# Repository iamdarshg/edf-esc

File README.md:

# EDF-ESC

Open hardware and firmware for a compact 98 mm × 58 mm, four-layer board with
two independent 6S sensorless BLDC/EDF controller channels.

> **Engineering prototype — do not fabricate or connect a battery.** The CAD
> currently contains documented placement placeholders, open nets, and DRC
> violations. It is not a validated 150 A design. See
> [`docs/cad-status.md`](docs/cad-status.md) for the exact blockers.

## Design targets

- two electrically independent power paths; no shared 300 A PCB segment;
- 18 × SFS06R025GF per channel, three devices per switch;
- DRV8300D gate driver and PY32F030K28U6TR controller per channel;
- high-side copper-shunt/INA190A3 current sensing with four-wire calibration;
- sensorless six-step control with PWM throttle and shared SPI/separate CS;
- shared 12 V gate supply, 5 V/8 A characterization-target BEC, and 3.3 V logic;
- JLCPCB/LCSC-first sourcing with Mouser alternatives and top-side assembly;
- top-side CNC copper reinforcement for every high-current path.

## What works today

The calculation engine, BOM/pin-mux contracts, host protocol, commutation table,
startup/control state machine, zero-cross detector, protection model, and both
channel configuration contracts are covered by native tests. KiCad 7.0.11
parses the generated review CAD and exports plots.

```sh
python3 -m venv .venv
.venv/bin/pip install -e '.[test]'
make test
.venv/bin/python -m edf_esc.cad
```

## Repository map

- `hardware/` — deterministic KiCad review project and design-rule contracts
- `firmware/` — tested portable control core and PY32 pin/configuration contract
- `host/` — SPI framing reference
- `bom/` — primary and alternate sourcing tables
- `calculations/` — gate, MOSFET, shunt, copper, and BEC estimates
- `docs/` — architecture, protocol, safety status, and source ledger

The progression to powered testing is intentionally gated: inspection, gate-only
testing, current-limited low-voltage switching, 3S motor testing, restricted 6S,
then thermal/electrical characterization. A numerical current ceiling is not a
continuous-current rating.

## License

MIT. See [`LICENSE`](LICENSE). Component datasheets and vendor SDK files are not
redistributed unless their licenses permit it.

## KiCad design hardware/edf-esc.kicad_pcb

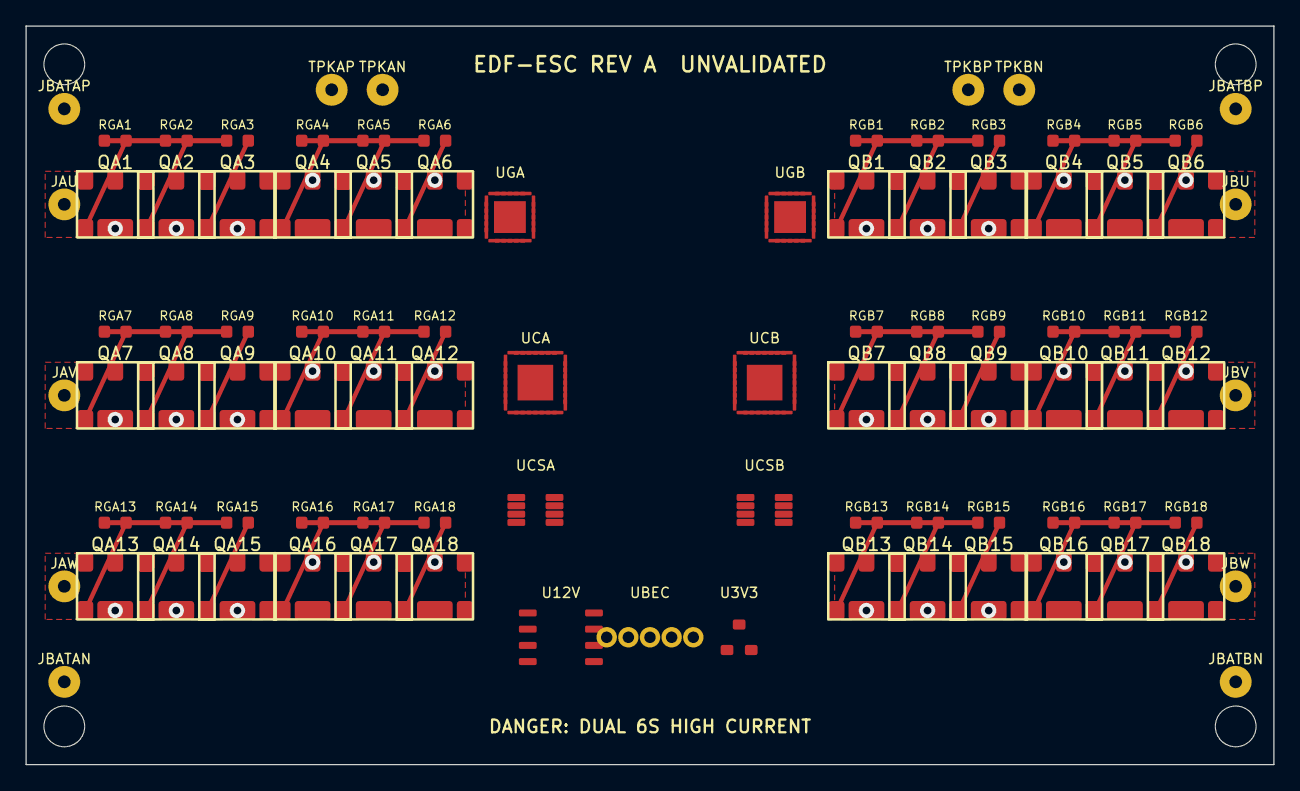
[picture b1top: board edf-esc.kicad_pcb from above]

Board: 4 copper layers, 98.0 x 58.0 mm, 99 parts (0 on the bottom side), 83 nets.

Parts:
H1, H2, H3, H4: M3; M3_NPTH
JAU: MOTOR_A_U; TESTPAD_2MM
JAV: MOTOR_A_V; TESTPAD_2MM
JAW: MOTOR_A_W; TESTPAD_2MM
JBATAN: BAT_A-; TESTPAD_2MM
JBATAP: BAT_A+; TESTPAD_2MM
JBATBN: BAT_B-; TESTPAD_2MM
JBATBP: BAT_B+; TESTPAD_2MM
JBU: MOTOR_B_U; TESTPAD_2MM
JBV: MOTOR_B_V; TESTPAD_2MM
JBW: MOTOR_B_W; TESTPAD_2MM
QA1, QA2, QA3, QA4, QA5, QA6, QA7, QA8, QA9, QA10, QA11, QA12, QA13, QA14, QA15, QA16, QA17, QA18: SFS06R025GF; PDFN56
QB1, QB2, QB3, QB4, QB5, QB6, QB7, QB8, QB9, QB10, QB11, QB12, QB13, QB14, QB15, QB16, QB17, QB18: SFS06R025GF; PDFN56
RGA1, RGA2, RGA3, RGA4, RGA5, RGA6, RGA7, RGA8, RGA9, RGA10, RGA11, RGA12, RGA13, RGA14, RGA15, RGA16, RGA17, RGA18: 4R7; R_0603
RGB1, RGB2, RGB3, RGB4, RGB5, RGB6, RGB7, RGB8, RGB9, RGB10, RGB11, RGB12, RGB13, RGB14, RGB15, RGB16, RGB17, RGB18: 4R7; R_0603
TPKAN: KELVIN_A-; TESTPAD_2MM
TPKAP: KELVIN_A+; TESTPAD_2MM
TPKBN: KELVIN_B-; TESTPAD_2MM
TPKBP: KELVIN_B+; TESTPAD_2MM
U3V3: XC6206P332MR; SOT23-3
U12V: XL1509-ADJ; SOIC8
UBEC: XL4016E1; TO220-5
UCA: PY32F030K28U6TR; QFN32
UCB: PY32F030K28U6TR; QFN32
UCSA: INA190A3IDDFR; TSOT23-8
UCSB: INA190A3IDDFR; TSOT23-8
UGA: DRV8300DRGER; QFN24
UGB: DRV8300DRGER; QFN24

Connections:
12V_GATE: UGA.4, UGB.4
12V_SW: U12V.1, U12V.2
+3V3: U3V3.2, UCA.1, UCB.1, UCSA.1, UCSA.2, UCSB.1, UCSB.2
BAT_A+: JBATAP.1, QA1.5, QA1.6, QA1.7, QA1.8, QA2.5, QA2.6, QA2.7, QA2.8, QA3.5, QA3.6, QA3.7, QA3.8, QA7.5, QA7.6, QA7.7, QA7.8, QA8.5, QA8.6, QA8.7, QA8.8, QA9.5, QA9.6, QA9.7, QA9.8, QA13.5, QA13.6, QA13.7, QA13.8, QA14.5, QA14.6, QA14.7, QA14.8, QA15.5, QA15.6, QA15.7, QA15.8, U12V.6, U12V.7, UBEC.4
BAT_A-: JBATAN.1, QA4.1, QA4.2, QA4.3, QA5.1, QA5.2, QA5.3, QA6.1, QA6.2, QA6.3, QA10.1, QA10.2, QA10.3, QA11.1, QA11.2, QA11.3, QA12.1, QA12.2, QA12.3, QA16.1, QA16.2, QA16.3, QA17.1, QA17.2, QA17.3, QA18.1, QA18.2, QA18.3
BAT_B+: JBATBP.1, QB1.5, QB1.6, QB1.7, QB1.8, QB2.5, QB2.6, QB2.7, QB2.8, QB3.5, QB3.6, QB3.7, QB3.8, QB7.5, QB7.6, QB7.7, QB7.8, QB8.5, QB8.6, QB8.7, QB8.8, QB9.5, QB9.6, QB9.7, QB9.8, QB13.5, QB13.6, QB13.7, QB13.8, QB14.5, QB14.6, QB14.7, QB14.8, QB15.5, QB15.6, QB15.7, QB15.8
BAT_B-: JBATBN.1, QB4.1, QB4.2, QB4.3, QB5.1, QB5.2, QB5.3, QB6.1, QB6.2, QB6.3, QB10.1, QB10.2, QB10.3, QB11.1, QB11.2, QB11.3, QB12.1, QB12.2, QB12.3, QB16.1, QB16.2, QB16.3, QB17.1, QB17.2, QB17.3, QB18.1, QB18.2, QB18.3
CURRENT_A: UCA.6, UCSA.5
CURRENT_B: UCB.6, UCSB.5
GND: U3V3.1, U12V.4, UBEC.1, UCA.16, UCA.31, UCA.33, UCB.16, UCB.31, UCB.33, UCSA.3, UCSA.4, UCSB.3, UCSB.4, UGA.5, UGA.6, UGA.25, UGB.5, UGB.6, UGB.25
G_A_UH: RGA1.1, RGA2.1, RGA3.1, UGA.19
G_A_UH_1: QA1.4, RGA1.2
G_A_UH_2: QA2.4, RGA2.2
G_A_UH_3: QA3.4, RGA3.2
G_A_UL: RGA4.1, RGA5.1, RGA6.1, UGA.11
G_A_UL_1: QA4.4, RGA4.2
G_A_UL_2: QA5.4, RGA5.2
G_A_UL_3: QA6.4, RGA6.2
G_A_VH: RGA7.1, RGA8.1, RGA9.1, UGA.16
G_A_VH_1: QA7.4, RGA7.2
G_A_VH_2: QA8.4, RGA8.2
G_A_VH_3: QA9.4, RGA9.2
G_A_VL: RGA10.1, RGA11.1, RGA12.1, UGA.10
G_A_VL_1: QA10.4, RGA10.2
G_A_VL_2: QA11.4, RGA11.2
G_A_VL_3: QA12.4, RGA12.2
G_A_WH: RGA13.1, RGA14.1, RGA15.1, UGA.13
G_A_WH_1: QA13.4, RGA13.2
G_A_WH_2: QA14.4, RGA14.2
G_A_WH_3: QA15.4, RGA15.2
G_A_WL: RGA16.1, RGA17.1, RGA18.1, UGA.9
G_A_WL_1: QA16.4, RGA16.2
G_A_WL_2: QA17.4, RGA17.2
G_A_WL_3: QA18.4, RGA18.2
G_B_UH: RGB1.1, RGB2.1, RGB3.1, UGB.19
G_B_UH_1: QB1.4, RGB1.2
G_B_UH_2: QB2.4, RGB2.2
G_B_UH_3: QB3.4, RGB3.2
G_B_UL: RGB4.1, RGB5.1, RGB6.1, UGB.11
G_B_UL_1: QB4.4, RGB4.2
G_B_UL_2: QB5.4, RGB5.2
G_B_UL_3: QB6.4, RGB6.2
G_B_VH: RGB7.1, RGB8.1, RGB9.1, UGB.16
G_B_VH_1: QB7.4, RGB7.2
G_B_VH_2: QB8.4, RGB8.2
G_B_VH_3: QB9.4, RGB9.2
G_B_VL: RGB10.1, RGB11.1, RGB12.1, UGB.10
G_B_VL_1: QB10.4, RGB10.2
G_B_VL_2: QB11.4, RGB11.2
G_B_VL_3: QB12.4, RGB12.2
G_B_WH: RGB13.1, RGB14.1, RGB15.1, UGB.13
G_B_WH_1: QB13.4, RGB13.2
G_B_WH_2: QB14.4, RGB14.2
G_B_WH_3: QB15.4, RGB15.2
G_B_WL: RGB16.1, RGB17.1, RGB18.1, UGB.9
G_B_WL_1: QB16.4, RGB16.2
G_B_WL_2: QB17.4, RGB17.2
G_B_WL_3: QB18.4, RGB18.2
KELVIN_A+: TPKAP.1, UCSA.7
KELVIN_A-: TPKAN.1, UCSA.8
KELVIN_B+: TPKBP.1, UCSB.7
KELVIN_B-: TPKBN.1, UCSB.8
MOTOR_A_U: JAU.1, QA1.1, QA1.2, QA1.3, QA2.1, QA2.2, QA2.3, QA3.1, QA3.2, QA3.3, QA4.5, QA4.6, QA4.7, QA4.8, QA5.5, QA5.6, QA5.7, QA5.8, QA6.5, QA6.6, QA6.7, QA6.8, UGA.18
MOTOR_A_V: JAV.1, QA7.1, QA7.2, QA7.3, QA8.1, QA8.2, QA8.3, QA9.1, QA9.2, QA9.3, QA10.5, QA10.6, QA10.7, QA10.8, QA11.5, QA11.6, QA11.7, QA11.8, QA12.5, QA12.6, QA12.7, QA12.8, UGA.15
MOTOR_A_W: JAW.1, QA13.1, QA13.2, QA13.3, QA14.1, QA14.2, QA14.3, QA15.1, QA15.2, QA15.3, QA16.5, QA16.6, QA16.7, QA16.8, QA17.5, QA17.6, QA17.7, QA17.8, QA18.5, QA18.6, QA18.7, QA18.8, UGA.12
MOTOR_B_U: JBU.1, QB1.1, QB1.2, QB1.3, QB2.1, QB2.2, QB2.3, QB3.1, QB3.2, QB3.3, QB4.5, QB4.6, QB4.7, QB4.8, QB5.5, QB5.6, QB5.7, QB5.8, QB6.5, QB6.6, QB6.7, QB6.8, UGB.18
MOTOR_B_V: JBV.1, QB7.1, QB7.2, QB7.3, QB8.1, QB8.2, QB8.3, QB9.1, QB9.2, QB9.3, QB10.5, QB10.6, QB10.7, QB10.8, QB11.5, QB11.6, QB11.7, QB11.8, QB12.5, QB12.6, QB12.7, QB12.8, UGB.15
MOTOR_B_W: JBW.1, QB13.1, QB13.2, QB13.3, QB14.1, QB14.2, QB14.3, QB15.1, QB15.2, QB15.3, QB16.5, QB16.6, QB16.7, QB16.8, QB17.5, QB17.6, QB17.7, QB17.8, QB18.5, QB18.6, QB18.7, QB18.8, UGB.12
PWM_A_UH: UCA.18, UGA.22
PWM_A_UL: UCA.13, UGA.1
PWM_A_VH: UCA.19, UGA.23
PWM_A_VL: UCA.14, UGA.2
PWM_A_WH: UCA.20, UGA.24
PWM_A_WL: UCA.15, UGA.3
PWM_B_UH: UCB.18, UGB.22
PWM_B_UL: UCB.13, UGB.1
PWM_B_VH: UCB.19, UGB.23
PWM_B_VL: UCB.14, UGB.2
PWM_B_WH: UCB.20, UGB.24
PWM_B_WL: UCB.15, UGB.3
SPI_MISO: UCA.3, UCB.3
SPI_MOSI: UCA.30, UCB.30
SPI_SCK: UCA.2, UCB.2
